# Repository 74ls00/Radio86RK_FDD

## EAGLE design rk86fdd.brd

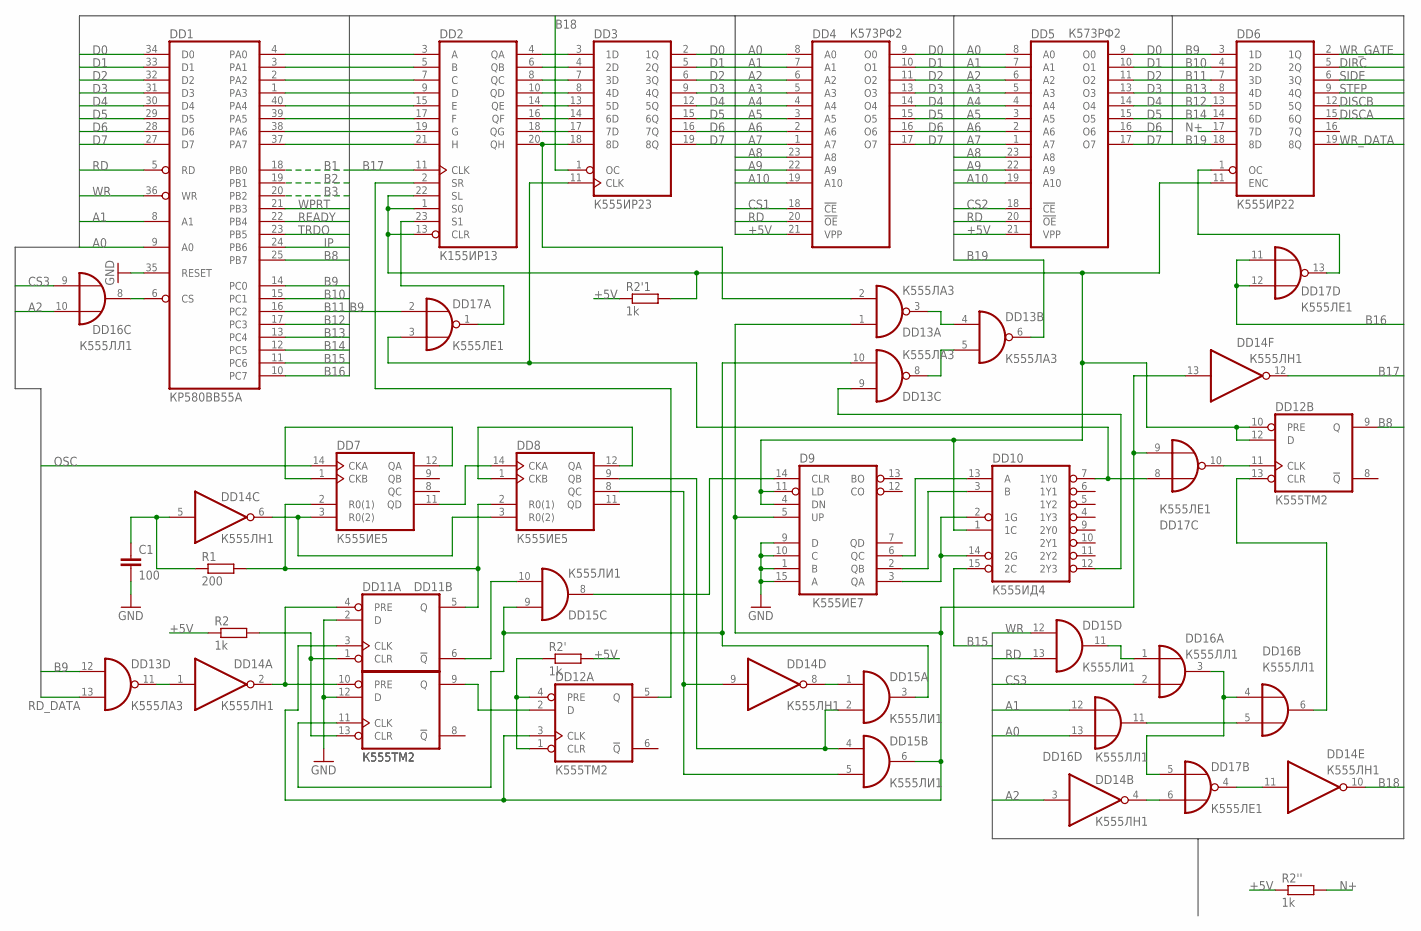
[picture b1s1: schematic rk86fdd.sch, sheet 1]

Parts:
C1: 100; C050-025X075
D9: К555ИЕ7; DIL16
DD1: КР580ВВ55А; DIL40
DD2: К155ИР13; DIL24-6
DD3: К555ИР23; DIL20
DD4, DD5: К573РФ2; DIL24
DD6: К555ИР22; DIL20
DD7, DD8: К555ИЕ5; DIL14
DD10: К555ИД4; DIL16
DD11, DD12: К555ТМ2; DIL14
DD13: К555ЛА3; DIL14
DD14: К555ЛН1; DIL14
DD15: К555ЛИ1; DIL14
DD16: К555ЛЛ1; DIL14
DD17: К555ЛЕ1; DIL14
R1: 200; R0805
R2, R2', R2'1, R2'': 1k; R0805

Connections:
1LOG: D9.4 (DN), D9.11 (LD), DD2.1 (S0), DD2.13 (CLR), DD2.22 (SL), DD6.11 (ENC), DD10.1 (1C), DD12.10 (PRE), DD12.12 (D), R2'1.2
+5V: DD4.21 (VPP), DD5.21 (VPP), R2.1, R2'.2, R2'1.1, R2''.1; also elsewhere on the board
A0: DD1.9 (A0), DD4.8 (A0), DD5.8 (A0), DD16.13 (I1); also elsewhere on the board
A1: DD1.8 (A1), DD4.7 (A1), DD5.7 (A1), DD16.12 (I0); also elsewhere on the board
A2: DD4.6 (A2), DD5.6 (A2), DD14.3 (I), DD16.10 (I1); also elsewhere on the board
A3: DD4.5 (A3), DD5.5 (A3); also elsewhere on the board
A4: DD4.4 (A4), DD5.4 (A4); also elsewhere on the board
A5: DD4.3 (A5), DD5.3 (A5); also elsewhere on the board
A6: DD4.2 (A6), DD5.2 (A6); also elsewhere on the board
A7: DD4.1 (A7), DD5.1 (A7); also elsewhere on the board
A8: DD4.23 (A8), DD5.23 (A8); also elsewhere on the board
A9: DD4.22 (A9), DD5.22 (A9); also elsewhere on the board
A10: DD4.19 (A10), DD5.19 (A10); also elsewhere on the board
B1: DD1.18 (PB0)
B2: DD1.19 (PB1)
B3: DD1.20 (PB2)
B8: DD1.25 (PB7), DD12.9 (Q)
B9: DD1.14 (PC0), DD6.3 (1D), DD13.12 (I0), DD17.2 (I0)
B10: DD1.15 (PC1), DD6.4 (2D)
B11: DD1.16 (PC2), DD6.7 (3D)
B12: DD1.17 (PC3), DD6.13 (5D)
B13: DD1.13 (PC4), DD6.8 (4D)
B14: DD1.12 (PC5), DD6.14 (6D)
B15: DD1.11 (PC6), DD10.15 (2C)
B16: DD1.10 (PC7), DD17.11 (I0), DD17.12 (I1)
B17: DD2.11 (CLK), DD14.12 (O)
B18: DD3.1 (OC), DD14.10 (O)
B19: DD6.18 (8D), DD13.6 (O)
CS1: DD4.18 (!CE); also elsewhere on the board
CS2: DD5.18 (!CE); also elsewhere on the board
CS3: DD16.2 (I1), DD16.9 (I0); also elsewhere on the board
D0: DD1.34 (D0), DD3.2 (1Q), DD4.9 (O0), DD5.9 (O0); also elsewhere on the board
D1: DD1.33 (D1), DD3.5 (2Q), DD4.10 (O1), DD5.10 (O1); also elsewhere on the board
D2: DD1.32 (D2), DD3.6 (3Q), DD4.11 (O2), DD5.11 (O2); also elsewhere on the board
D3: DD1.31 (D3), DD3.9 (4Q), DD4.13 (O3), DD5.13 (O3); also elsewhere on the board
D4: DD1.30 (D4), DD3.12 (5Q), DD4.14 (O4), DD5.14 (O4); also elsewhere on the board
D5: DD1.29 (D5), DD3.15 (6Q), DD4.15 (O5), DD5.15 (O5); also elsewhere on the board
D6: DD1.28 (D6), DD3.16 (7Q), DD4.16 (O6), DD5.16 (O6); also elsewhere on the board
D7: DD1.27 (D7), DD3.19 (8Q), DD4.17 (O7), DD5.17 (O7); also elsewhere on the board
DD12Q5: DD2.2 (SR), DD12.5 (Q)
DIRC: DD6.5 (2Q); also elsewhere on the board
DISCA: DD6.15 (6Q); also elsewhere on the board
DISCB: DD6.12 (5Q); also elsewhere on the board
GND: C1.2, D9.1 (B), D9.9 (D), D9.10 (C), D9.15 (A), DD1.35 (RESET), DD11.2 (D), DD11.12 (D); also elsewhere on the board
IP: DD1.24 (PB6); also elsewhere on the board
LOG1: DD12.1 (CLR), DD12.4 (PRE), R2'.1
unnamed: DD13.11 (O), DD14.1 (I)
unnamed: DD2.4 (QA), DD3.3 (1D)
unnamed: DD2.6 (QB), DD3.4 (2D)
unnamed: DD2.8 (QC), DD3.7 (3D)
unnamed: DD2.10 (QD), DD3.8 (4D)
unnamed: DD2.14 (QE), DD3.13 (5D)
unnamed: DD2.16 (QF), DD3.14 (6D)
unnamed: DD2.18 (QG), DD3.17 (7D)
unnamed: DD2.20 (QH), DD3.18 (8D), DD13.2 (I1)
unnamed: DD7.1 (CKB), DD7.12 (QA)
unnamed: DD8.1 (CKB), DD8.12 (QA)
unnamed: DD1.4 (PA0), DD2.3 (A)
unnamed: DD1.3 (PA1), DD2.5 (B)
unnamed: DD1.2 (PA2), DD2.7 (C)
unnamed: DD1.1 (PA3), DD2.9 (D)
unnamed: DD7.11 (QD), DD8.14 (CKA)
unnamed: DD7.3 (R0(2)), DD8.3 (R0(2)), DD14.6 (O)
unnamed: DD1.40 (PA4), DD2.15 (E)
unnamed: DD1.39 (PA5), DD2.17 (F)
unnamed: DD1.38 (PA6), DD2.19 (G)
unnamed: DD1.37 (PA7), DD2.21 (H)
unnamed: DD7.2 (R0(1)), DD8.2 (R0(1)), DD11.5 (Q), R1.2
unnamed: D9.5 (UP), DD11.3 (CLK), DD12.3 (CLK), DD13.1 (I0), DD14.13 (I), DD15.6 (O), DD17.9 (I1)
unnamed: DD11.1 (CLR), DD11.13 (CLR), R2.2
unnamed: DD11.9 (Q), DD12.2 (D)
unnamed: DD15.11 (O), DD16.1 (I0)
unnamed: DD6.1 (OC), DD17.13 (O)
unnamed: C1.1, DD14.5 (I), R1.1
unnamed: DD2.23 (S1), DD17.1 (O)
unnamed: DD3.11 (CLK), DD10.7 (1Y0), DD17.3 (I1), DD17.8 (I0)
unnamed: DD11.4 (PRE), DD11.10 (PRE), DD14.2 (O)
unnamed: DD16.3 (O), DD16.4 (I0), DD17.5 (I0)
unnamed: DD1.6 (CS), DD16.8 (O)
unnamed: D9.3 (QA), DD10.2 (1G), DD10.14 (2G)
unnamed: DD11.6 (!Q), DD15.10 (I1)
unnamed: DD11.11 (CLK), DD13.10 (I1), DD15.3 (O), DD15.9 (I0)
unnamed: DD12.11 (CLK), DD17.10 (O)
unnamed: DD16.5 (I1), DD16.11 (O)
unnamed: DD14.4 (O), DD17.6 (I1)
unnamed: DD12.13 (CLR), DD16.6 (O)
unnamed: DD14.11 (I), DD17.4 (O)
unnamed: DD8.9 (QB), DD15.2 (I1), DD15.4 (I0)
unnamed: DD14.8 (O), DD15.1 (I0)
unnamed: DD8.8 (QC), DD14.9 (I), DD15.5 (I1)
unnamed: DD13.3 (O), DD13.4 (I0)
unnamed: DD13.5 (I1), DD13.8 (O)
unnamed: D9.14 (CLR), DD15.8 (O)
unnamed: D9.2 (QB), DD10.3 (B)
unnamed: D9.6 (QC), DD10.13 (A)
unnamed: DD10.12 (2Y3), DD13.9 (I0)
N+: DD6.17 (7D), R2''.2
OSC: DD7.14 (CKA); also elsewhere on the board
RD: DD1.5 (RD), DD4.20 (!OE), DD5.20 (!OE), DD15.13 (I1); also elsewhere on the board
RD_DATA: DD13.13 (I1); also elsewhere on the board
READY: DD1.22 (PB4); also elsewhere on the board
SIDE: DD6.6 (3Q); also elsewhere on the board
STEP: DD6.9 (4Q); also elsewhere on the board
TRDO: DD1.23 (PB5); also elsewhere on the board
WPRT: DD1.21 (PB3); also elsewhere on the board
WR: DD1.36 (WR), DD15.12 (I0); also elsewhere on the board
WR_DATA: DD6.19 (8Q); also elsewhere on the board
WR_GATE: DD6.2 (1Q); also elsewhere on the board

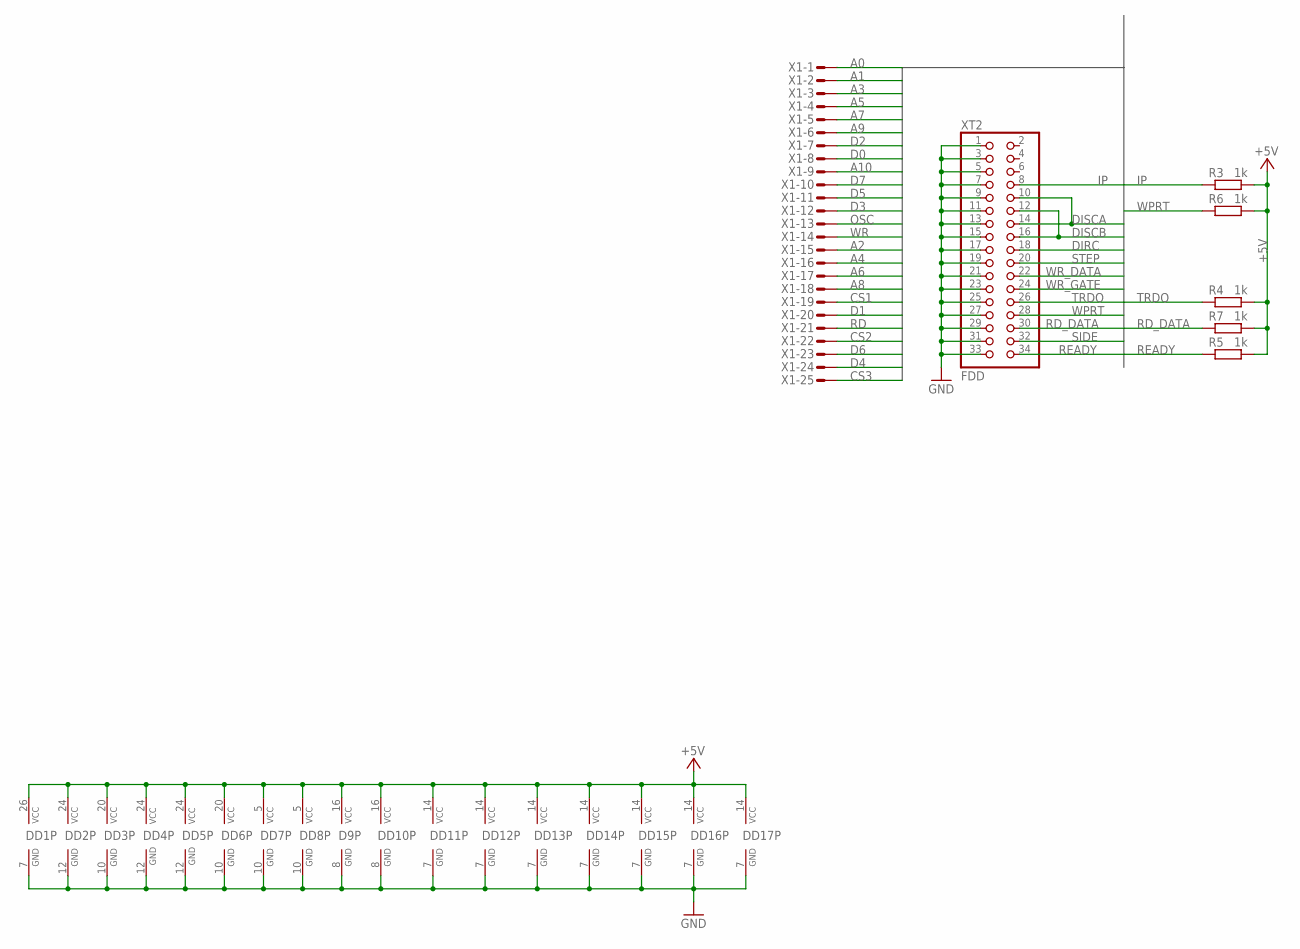
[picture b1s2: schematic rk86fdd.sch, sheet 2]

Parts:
D9: К555ИЕ7; DIL16
DD1: КР580ВВ55А; DIL40
DD2: К155ИР13; DIL24-6
DD3: К555ИР23; DIL20
DD4, DD5: К573РФ2; DIL24
DD6: К555ИР22; DIL20
DD7, DD8: К555ИЕ5; DIL14
DD10: К555ИД4; DIL16
DD11, DD12: К555ТМ2; DIL14
DD13: К555ЛА3; DIL14
DD14: К555ЛН1; DIL14
DD15: К555ЛИ1; DIL14
DD16: К555ЛЛ1; DIL14
DD17: К555ЛЕ1; DIL14
R3, R4, R5, R6, R7: 1k; R0805
X1: M25HPS; M25HP
XT2: FDD; 2X17

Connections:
+5V: D9.16 (VCC), DD1.26 (VCC), DD2.24 (VCC), DD3.20 (VCC), DD4.24 (VCC), DD5.24 (VCC), DD6.20 (VCC), DD7.5 (VCC), DD8.5 (VCC), DD10.16 (VCC), DD11.14 (VCC), DD12.14 (VCC), DD13.14 (VCC), DD14.14 (VCC), DD15.14 (VCC), DD16.14 (VCC), DD17.14 (VCC), R3.2, R4.2, R5.2, R6.2, R7.2; also elsewhere on the board
A0: X1.1; also elsewhere on the board
A1: X1.2; also elsewhere on the board
A2: X1.15; also elsewhere on the board
A3: X1.3; also elsewhere on the board
A4: X1.16; also elsewhere on the board
A5: X1.4; also elsewhere on the board
A6: X1.17; also elsewhere on the board
A7: X1.5; also elsewhere on the board
A8: X1.18; also elsewhere on the board
A9: X1.6; also elsewhere on the board
A10: X1.9; also elsewhere on the board
CS1: X1.19; also elsewhere on the board
CS2: X1.22; also elsewhere on the board
CS3: X1.25; also elsewhere on the board
D0: X1.8; also elsewhere on the board
D1: X1.20; also elsewhere on the board
D2: X1.7; also elsewhere on the board
D3: X1.12; also elsewhere on the board
D4: X1.24; also elsewhere on the board
D5: X1.11; also elsewhere on the board
D6: X1.23; also elsewhere on the board
D7: X1.10; also elsewhere on the board
DIRC: XT2.18; also elsewhere on the board
DISCA: XT2.10, XT2.14; also elsewhere on the board
DISCB: XT2.12, XT2.16; also elsewhere on the board
GND: D9.8 (GND), DD1.7 (GND), DD2.12 (GND), DD3.10 (GND), DD4.12 (GND), DD5.12 (GND), DD6.10 (GND), DD7.10 (GND), DD8.10 (GND), DD10.8 (GND), DD11.7 (GND), DD12.7 (GND), DD13.7 (GND), DD14.7 (GND), DD15.7 (GND), DD16.7 (GND), DD17.7 (GND), XT2.1, XT2.3, XT2.5, XT2.7, XT2.9, XT2.11, XT2.13, XT2.15, XT2.17, XT2.19, XT2.21, XT2.23, XT2.25, XT2.27, XT2.29, XT2.31, XT2.33; also elsewhere on the board
IP: R3.1, XT2.8; also elsewhere on the board
OSC: X1.13; also elsewhere on the board
RD: X1.21; also elsewhere on the board
RD_DATA: R7.1, XT2.30; also elsewhere on the board
READY: R5.1, XT2.34; also elsewhere on the board
SIDE: XT2.32; also elsewhere on the board
STEP: XT2.20; also elsewhere on the board
TRDO: R4.1, XT2.26; also elsewhere on the board
WPRT: R6.1, XT2.28; also elsewhere on the board
WR: X1.14; also elsewhere on the board
WR_DATA: XT2.22; also elsewhere on the board
WR_GATE: XT2.24; also elsewhere on the board

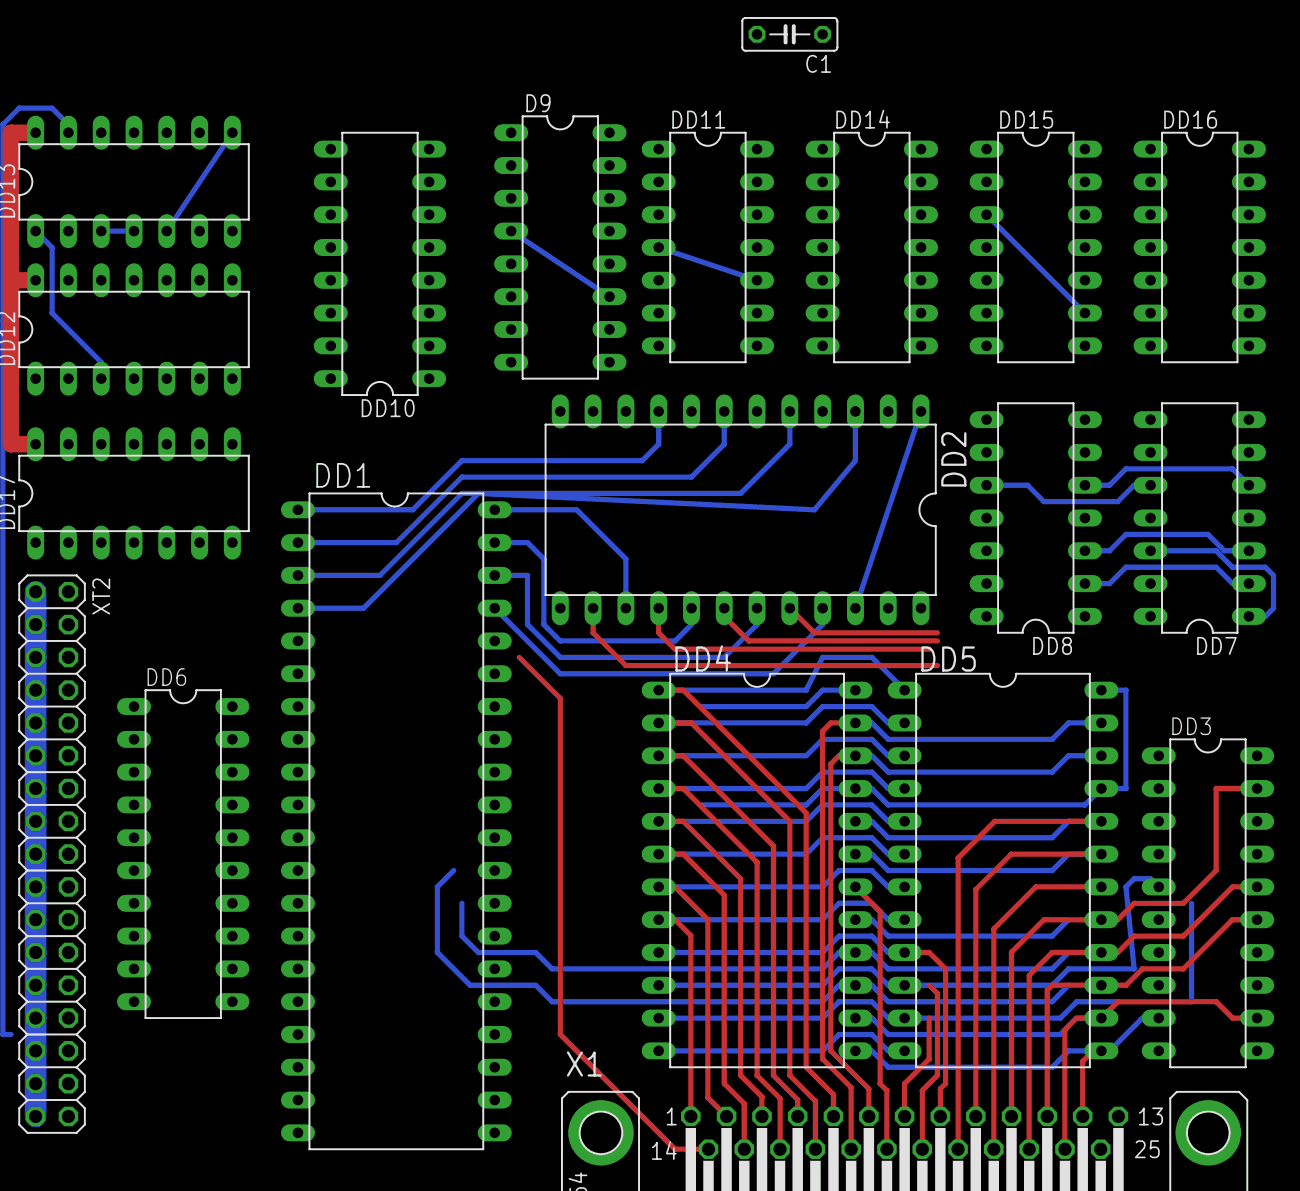
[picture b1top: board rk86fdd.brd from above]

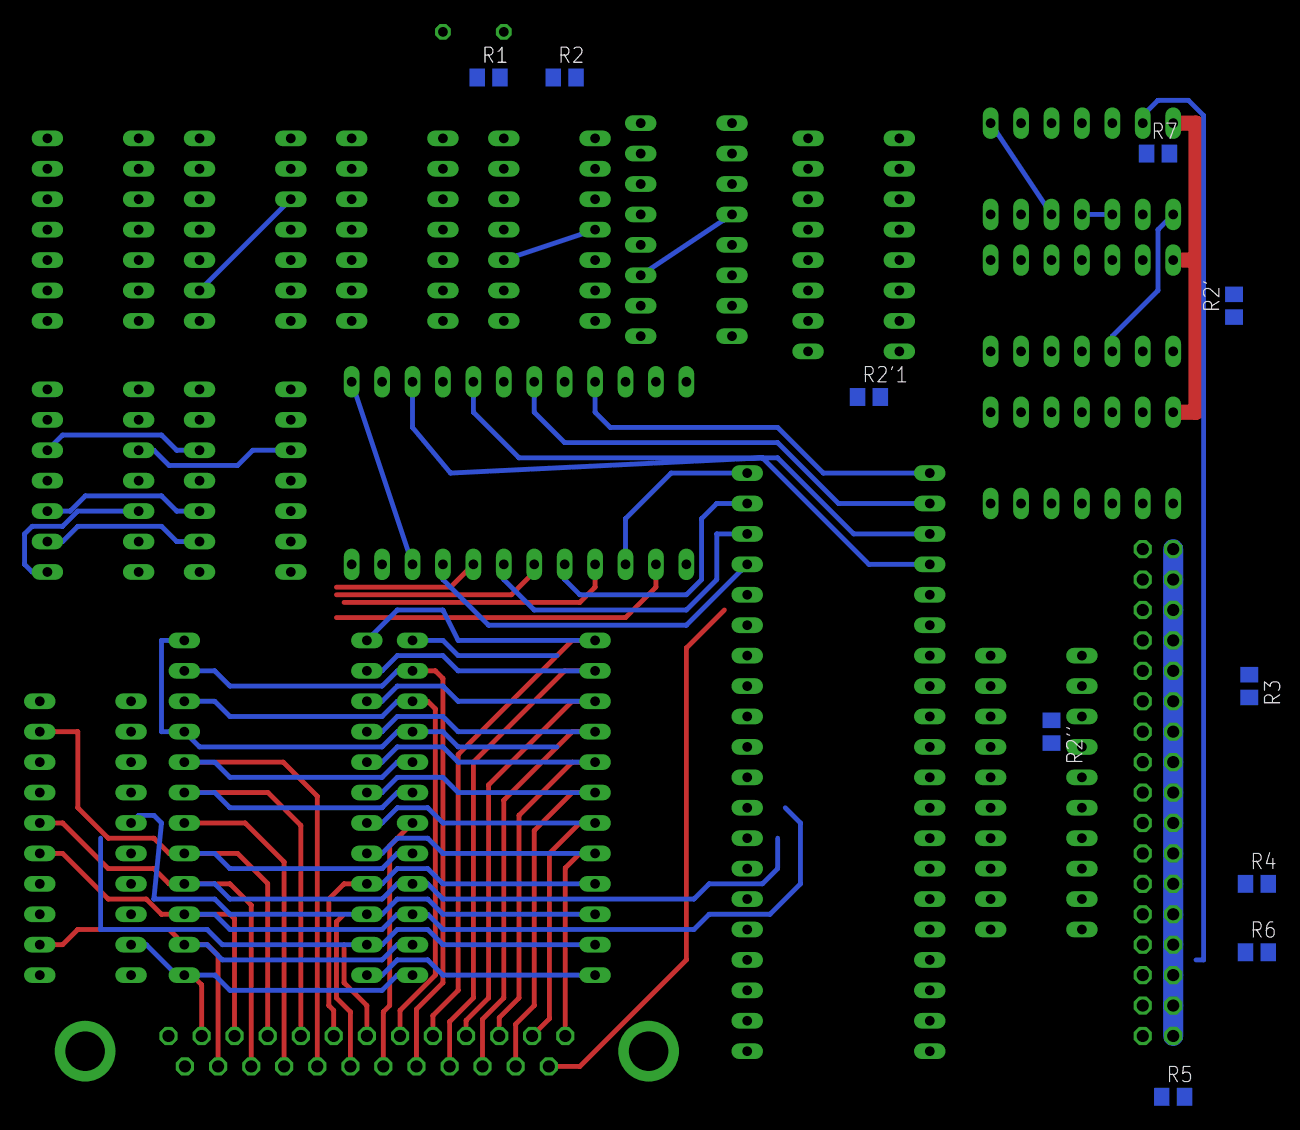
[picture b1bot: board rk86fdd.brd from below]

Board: 2 copper layers, 30 parts (10 on the bottom side), 105 nets.
